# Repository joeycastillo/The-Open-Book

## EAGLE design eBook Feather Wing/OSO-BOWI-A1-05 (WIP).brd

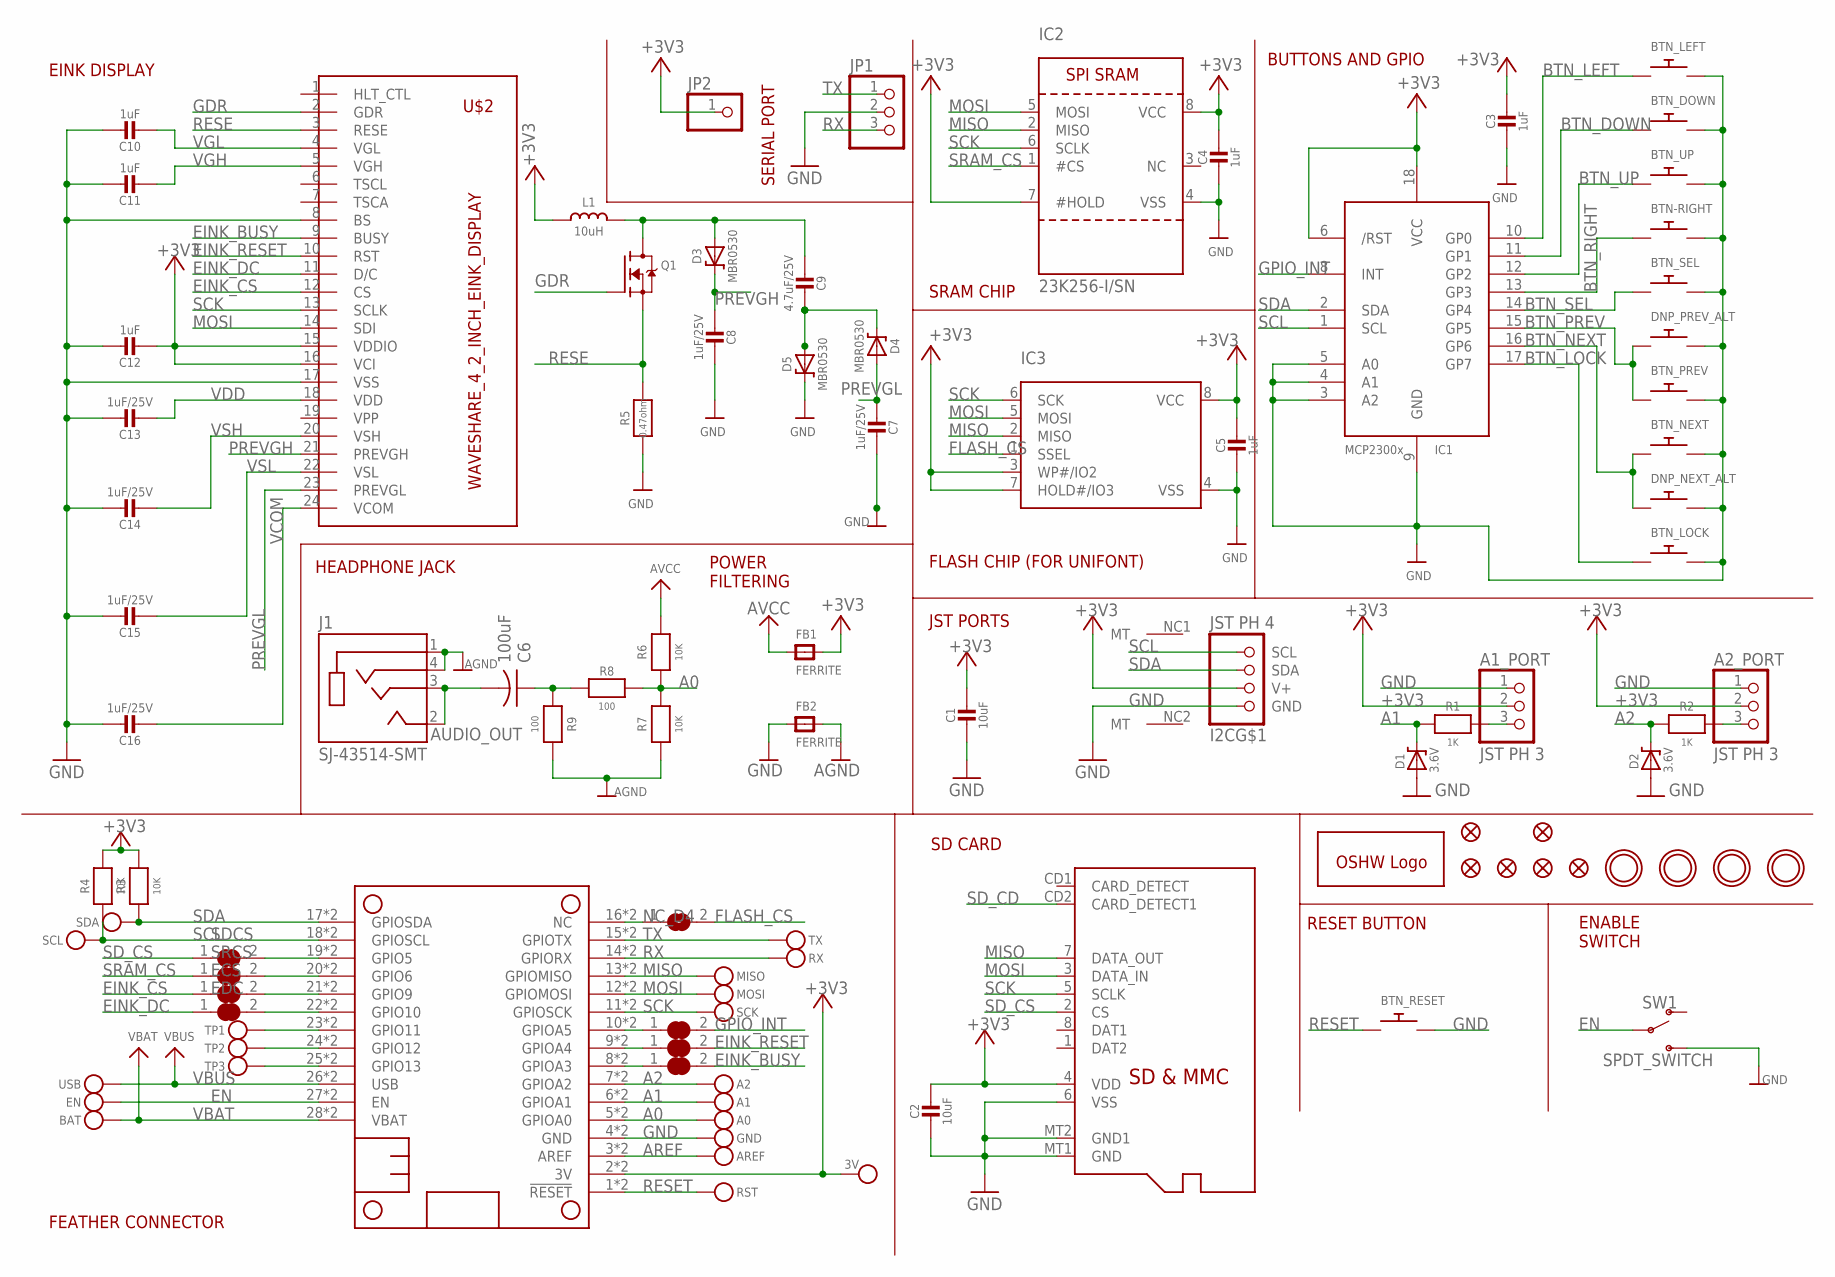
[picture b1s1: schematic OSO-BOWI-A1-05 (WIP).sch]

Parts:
3V: MICROBUILDER_TESTPOINT1.5X2.0MM_NOCREAM; MICROBUILDER_PAD-1.5X2.0
A0, A1, A2: MICROBUILDER_TESTPOINT1.5X2.0MM_NOCREAM; MICROBUILDER_PAD-1.5X2.0
A1_PORT, A2_PORT: JST PH 3; JSTPH3
AREF: MICROBUILDER_TESTPOINT1.5X2.0MM_NOCREAM; MICROBUILDER_PAD-1.5X2.0
BAT: MICROBUILDER_TESTPOINT1.5X2.0MM_NOCREAM; MICROBUILDER_PAD-1.5X2.0
BCS: SOLDERJUMPER_OPEN
BTN-RIGHT: SWITCH_PUSHBUTTONEVQ-PE; TACT_PANA-EVQ
BTN_DOWN: SWITCH_PUSHBUTTONEVQ-PE; TACT_PANA-EVQ
BTN_LEFT: SWITCH_PUSHBUTTONEVQ-PE; TACT_PANA-EVQ
BTN_LOCK: SWITCH_PUSHBUTTONC&K_KSS; BTN_CK_KSS
BTN_NEXT: SWITCH_PUSHBUTTONEVQ-PE; TACT_PANA-EVQ
BTN_PREV: SWITCH_PUSHBUTTONEVQ-PE; TACT_PANA-EVQ
BTN_RESET: SWITCH_PUSHBUTTONC&K_KSS; BTN_CK_KSS
BTN_SEL: SWITCH_PUSHBUTTONEVQ-PE; TACT_PANA-EVQ
BTN_UP: SWITCH_PUSHBUTTONEVQ-PE; TACT_PANA-EVQ
C1: 10uF; 0805-NO
C2: 10uF; 0805_10MGAP
C3, C4, C5: 1uF; 0805_10MGAP
C6: 100uF; C1210
C7, C8, C13, C14, C15, C16: 1uF/25V; 0805-NO
C9: 4.7uF/25V; 0805-NO
C10, C11, C12: 1uF; 0805-NO
D1, D2: 3.6V; SOD-123
D3, D4, D5: MBR0530; SOD-123
DNP_NEXT_ALT: SPST_TACTILE_SWITCHRA; TL3330AF130QG
DNP_PREV_ALT: SPST_TACTILE_SWITCHRA; TL3330AF130QG
EBSY: MICROBUILDER_SOLDERJUMPER_CLOSED; MICROBUILDER_SOLDERJUMPER_CLOSEDWIRE
ECS: MICROBUILDER_SOLDERJUMPER_CLOSED; MICROBUILDER_SOLDERJUMPER_CLOSEDWIRE
EDC: MICROBUILDER_SOLDERJUMPER_CLOSED; MICROBUILDER_SOLDERJUMPER_CLOSEDWIRE
EN: MICROBUILDER_TESTPOINT1.5X2.0MM_NOCREAM; MICROBUILDER_PAD-1.5X2.0
ERST: MICROBUILDER_SOLDERJUMPER_CLOSED; MICROBUILDER_SOLDERJUMPER_CLOSEDWIRE
FB1, FB2: FERRITE; 0805
FID1, FID2, FID3, FID4, FID5, FID6: FIDUCIAL_1MM
GND: MICROBUILDER_TESTPOINT1.5X2.0MM_NOCREAM; MICROBUILDER_PAD-1.5X2.0
GOLD_ORB_SM1: OSHWLOGOLOGO5MM; OSHW_5MM
I2C: JST PH 4; JSTPH4
IC1: MCP23008/SO; SO18W
IC2: 23K256-I/SN; SOIC8_150MIL
IC3: MICROBUILDER_SPIFLASH_SOIC8; MICROBUILDER_SOIC8_150MIL
INT: MICROBUILDER_SOLDERJUMPER_CLOSED; MICROBUILDER_SOLDERJUMPER_CLOSEDWIRE
J1: SJ-43514-SMT; CUI_SJ-43514-SMT
JP1: PINHD-1X3; 1X03
JP2: PINHD-1X1; 1X01
L1: 10uH; MICROBUILDER_INDUCTOR_4X4MM_NR401_BIGPADS
MICROSD: MICROSD
MISO: MICROBUILDER_TESTPOINT1.5X2.0MM_NOCREAM; MICROBUILDER_PAD-1.5X2.0
MOSI: MICROBUILDER_TESTPOINT1.5X2.0MM_NOCREAM; MICROBUILDER_PAD-1.5X2.0
MS1: MICROBUILDER_FEATHERWING_SMTDUAL; MICROBUILDER_FEATHERWING_SMT2
Q1: IRLML0100; SOT23-3
R1, R2: 1K; _0805MP
R3, R4, R6, R7: 10K; _0805MP
R5: 0.47ohm; 0805_10MGAP
R8, R9: 100; _0805MP
RST: MICROBUILDER_TESTPOINT1.5X2.0MM_NOCREAM; MICROBUILDER_PAD-1.5X2.0
RX: MICROBUILDER_TESTPOINT1.5X2.0MM_NOCREAM; MICROBUILDER_PAD-1.5X2.0
SCK: MICROBUILDER_TESTPOINT1.5X2.0MM_NOCREAM; MICROBUILDER_PAD-1.5X2.0
SCL: MICROBUILDER_TESTPOINT1.5X2.0MM_NOCREAM; MICROBUILDER_PAD-1.5X2.0
SDA: MICROBUILDER_TESTPOINT1.5X2.0MM_NOCREAM; MICROBUILDER_PAD-1.5X2.0
SDCS: MICROBUILDER_SOLDERJUMPER_CLOSED; MICROBUILDER_SOLDERJUMPER_CLOSEDWIRE
SRCS: MICROBUILDER_SOLDERJUMPER_CLOSED; MICROBUILDER_SOLDERJUMPER_CLOSEDWIRE
SW1: SPDT_SWITCH; A10767
TP1, TP2, TP3: MICROBUILDER_TESTPOINT1.5X2.0MM_NOCREAM; MICROBUILDER_PAD-1.5X2.0
TX: MICROBUILDER_TESTPOINT1.5X2.0MM_NOCREAM; MICROBUILDER_PAD-1.5X2.0
U$1, U$4, U$5, U$7: MOUNTINGHOLE2.5; MOUNTINGHOLE_2.5_PLATED
U$2: WAVESHARE_4_2_INCH_EINK_DISPLAY; EINK_DISPLAY_4_2IN
USB: MICROBUILDER_TESTPOINT1.5X2.0MM_NOCREAM; MICROBUILDER_PAD-1.5X2.0

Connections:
+3V3: 3V.P$1, A1_PORT.2, A2_PORT.2, C1.1, C2.1, C3.1, C4.1, C5.1, C12.2, FB1.2, I2C.2 (V+), IC1.6 (/RST), IC1.18 (VCC), IC2.7 (#HOLD), IC2.8 (VCC), IC3.3 (WP#/IO2), IC3.7 (HOLD#/IO3), IC3.8 (VCC), JP2.1, L1.P$1 (1), MICROSD.4 (VDD), MS1.2 (3V), MS1.2' (3V), R3.1, R4.1, U$2.15 (VDDIO), U$2.16 (VCI)
A0: A0.P$1, MS1.5 (GPIOA0), MS1.5' (GPIOA0), R6.2, R7.1, R8.1
A1: A1.P$1, D1.C, MS1.6 (GPIOA1), MS1.6' (GPIOA1), R1.2
A1_: A1_PORT.3, R1.1
A2: A2.P$1, D2.C, MS1.7 (GPIOA2), MS1.7' (GPIOA2), R2.2
A2_: A2_PORT.3, R2.1
AGND: FB2.2, J1.1 (SLEEVE), J1.4 (RING2), R7.2, R9.1
AREF: AREF.P$1, MS1.3 (AREF), MS1.3' (AREF)
AUDIO_OUT: C6.2, J1.2 (TIP), J1.3 (RING1)
AVCC: FB1.1, R6.1
BTN_DOWN: BTN_DOWN.P$1, IC1.11 (GP1)
BTN_LEFT: BTN_LEFT.P$1, IC1.10 (GP0)
BTN_LOCK: BTN_LOCK.P$1, IC1.17 (GP7)
BTN_NEXT: BTN_NEXT.P$1, DNP_NEXT_ALT.P$1, IC1.16 (GP6)
BTN_PREV: BTN_PREV.P$1, DNP_PREV_ALT.P$1, IC1.15 (GP5)
BTN_RIGHT: BTN-RIGHT.P$1, IC1.13 (GP3)
BTN_SEL: BTN_SEL.P$1, IC1.14 (GP4)
BTN_UP: BTN_UP.P$1, IC1.12 (GP2)
EINK_BUSY: EBSY.2, U$2.9 (BUSY)
EINK_CS: ECS.1, U$2.12 (CS)
EINK_DC: EDC.1, U$2.11 (D/C)
EINK_RESET: ERST.2, U$2.10 (RST)
EN: EN.P$1, MS1.27 (EN), MS1.27' (EN), SW1.P$2
FLASH_CS: BCS.2, IC3.1 (SSEL)
GDR: Q1.1 (G), U$2.2 (GDR)
GND: A1_PORT.1, A2_PORT.1, BTN-RIGHT.P$2, BTN_DOWN.P$2, BTN_LEFT.P$2, BTN_LOCK.P$2, BTN_NEXT.P$2, BTN_PREV.P$2, BTN_RESET.P$2, BTN_SEL.P$2, BTN_UP.P$2, C1.2, C2.2, C3.2, C4.2, C5.2, C7.2, C8.2, C10.1, C11.1, C12.1, C13.1, C14.1, C15.1, C16.1, D1.A, D2.A, D5.C, DNP_NEXT_ALT.P$2, DNP_PREV_ALT.P$2, FB2.1, GND.P$1, I2C.1 (GND), IC1.3 (A2), IC1.4 (A1), IC1.5 (A0), IC1.9 (GND), IC2.4 (VSS), IC3.4 (VSS), JP1.2, MICROSD.6 (VSS), MICROSD.MT1 (GND), MICROSD.MT2 (GND1), MS1.4 (GND), MS1.4' (GND), R5.2, SW1.P$3 (S), U$2.8 (BS), U$2.17 (VSS)
GPIO_INT: IC1.8 (INT), INT.2
MISO: IC2.2 (MISO), IC3.2 (MISO), MICROSD.7 (DATA_OUT), MISO.P$1, MS1.13 (GPIOMISO), MS1.13' (GPIOMISO)
MOSI: IC2.5 (MOSI), IC3.5 (MOSI), MICROSD.3 (DATA_IN), MOSI.P$1, MS1.12 (GPIOMOSI), MS1.12' (GPIOMOSI), U$2.14 (SDI)
unnamed: C6.1, R8.2, R9.2
unnamed: C9.2, D4.C, D5.A
unnamed: C9.1, D3.A, L1.P$2 (2), Q1.3 (D)
unnamed: MS1.25 (GPIO13), MS1.25' (GPIO13), TP3.P$1
unnamed: MS1.24 (GPIO12), MS1.24' (GPIO12), TP2.P$1
unnamed: MS1.23 (GPIO11), MS1.23' (GPIO11), TP1.P$1
NC_D4: BCS.1, MS1.16 (NC), MS1.16' (NC)
PREVGH: C8.1, D3.C, U$2.21 (PREVGH)
PREVGL: C7.1, D4.A, U$2.23 (PREVGL)
RESE: Q1.2 (S), R5.1, U$2.3 (RESE)
RESET: BTN_RESET.P$1, MS1.1 (!RESET), MS1.1' (!RESET), RST.P$1
RX: JP1.3, MS1.14 (GPIORX), MS1.14' (GPIORX), RX.P$1
SCK: IC2.6 (SCLK), IC3.6 (SCK), MICROSD.5 (SCLK), MS1.11 (GPIOSCK), MS1.11' (GPIOSCK), SCK.P$1, U$2.13 (SCLK)
SCL: I2C.4 (SCL), IC1.1 (SCL), MS1.18 (GPIOSCL), MS1.18' (GPIOSCL), R4.2, SCL.P$1
SDA: I2C.3 (SDA), IC1.2 (SDA), MS1.17 (GPIOSDA), MS1.17' (GPIOSDA), R3.2, SDA.P$1
SD_CD: MICROSD.CD2 (CARD_DETECT1)
SD_CS: MICROSD.2 (CS), SDCS.1
SRAM_CS: IC2.1 (#CS), SRCS.1
TX: JP1.1, MS1.15 (GPIOTX), MS1.15' (GPIOTX), TX.P$1
VBAT: BAT.P$1, MS1.28 (VBAT), MS1.28' (VBAT)
VBUS: MS1.26 (USB), MS1.26' (USB), USB.P$1
VCOM: C16.2, U$2.24 (VCOM)
VDD: C13.2, U$2.18 (VDD)
VGH: C11.2, U$2.5 (VGH)
VGL: C10.2, U$2.4 (VGL)
VSH: C14.2, U$2.20 (VSH)
VSL: C15.2, U$2.22 (VSL)
_EINK_BUSY: EBSY.1, MS1.8 (GPIOA3), MS1.8' (GPIOA3)
_EINK_CS: ECS.2, MS1.21 (GPIO9), MS1.21' (GPIO9)
_EINK_DC: EDC.2, MS1.22 (GPIO10), MS1.22' (GPIO10)
_EINK_RESET: ERST.1, MS1.9 (GPIOA4), MS1.9' (GPIOA4)
_GPIO_INT: INT.1, MS1.10 (GPIOA5), MS1.10' (GPIOA5)
_SD_CS: MS1.19 (GPIO5), MS1.19' (GPIO5), SDCS.2
_SRAM_CS: MS1.20 (GPIO6), MS1.20' (GPIO6), SRCS.2

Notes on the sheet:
FEATHER CONNECTOR
SD CARD
EINK DISPLAY
HEADPHONE JACK
RESET BUTTON
ENABLE SWITCH
POWER FILTERING
BUTTONS AND GPIO
JST PORTS
SRAM CHIP
FLASH CHIP (FOR UNIFONT)
SERIAL PORT

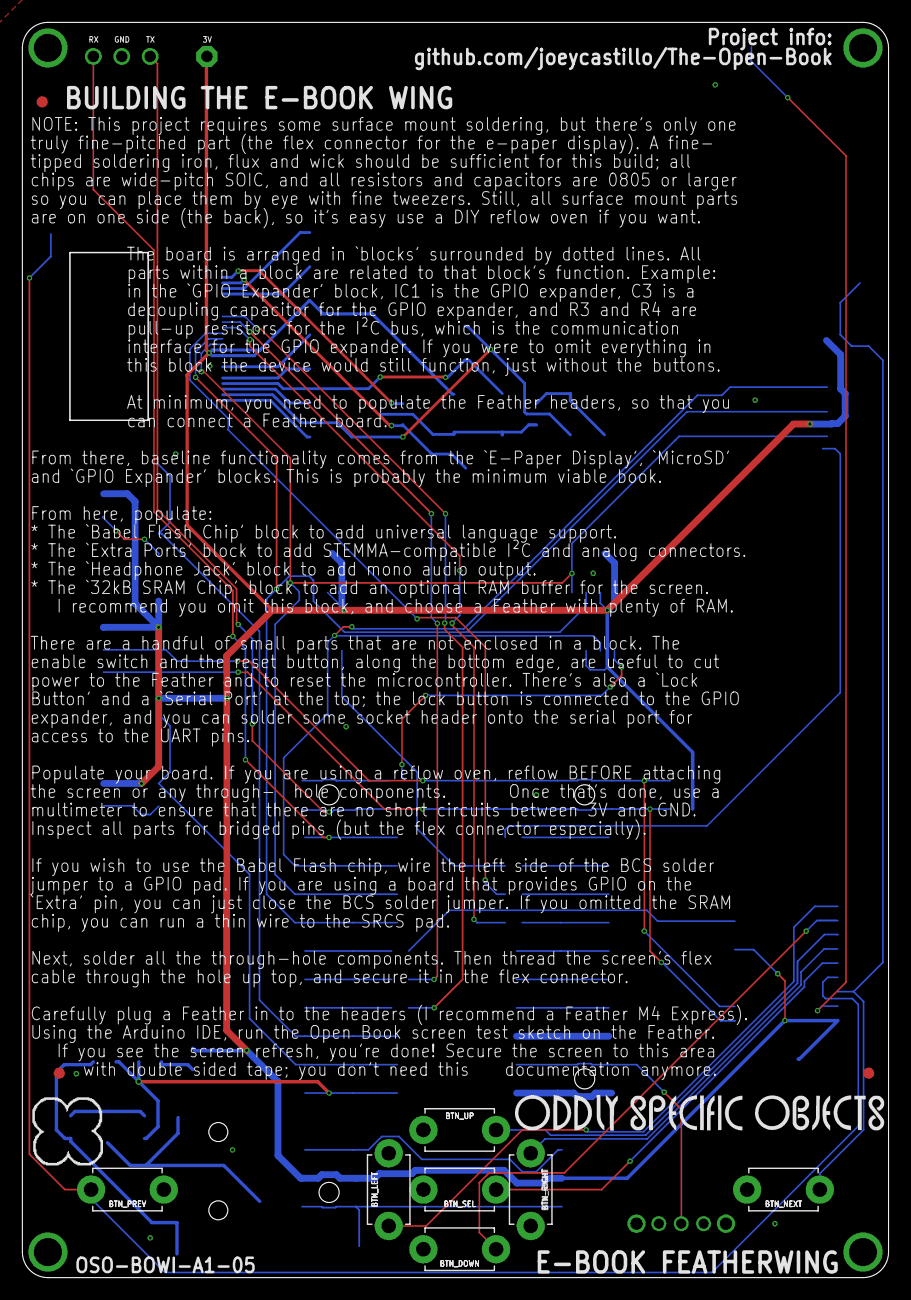
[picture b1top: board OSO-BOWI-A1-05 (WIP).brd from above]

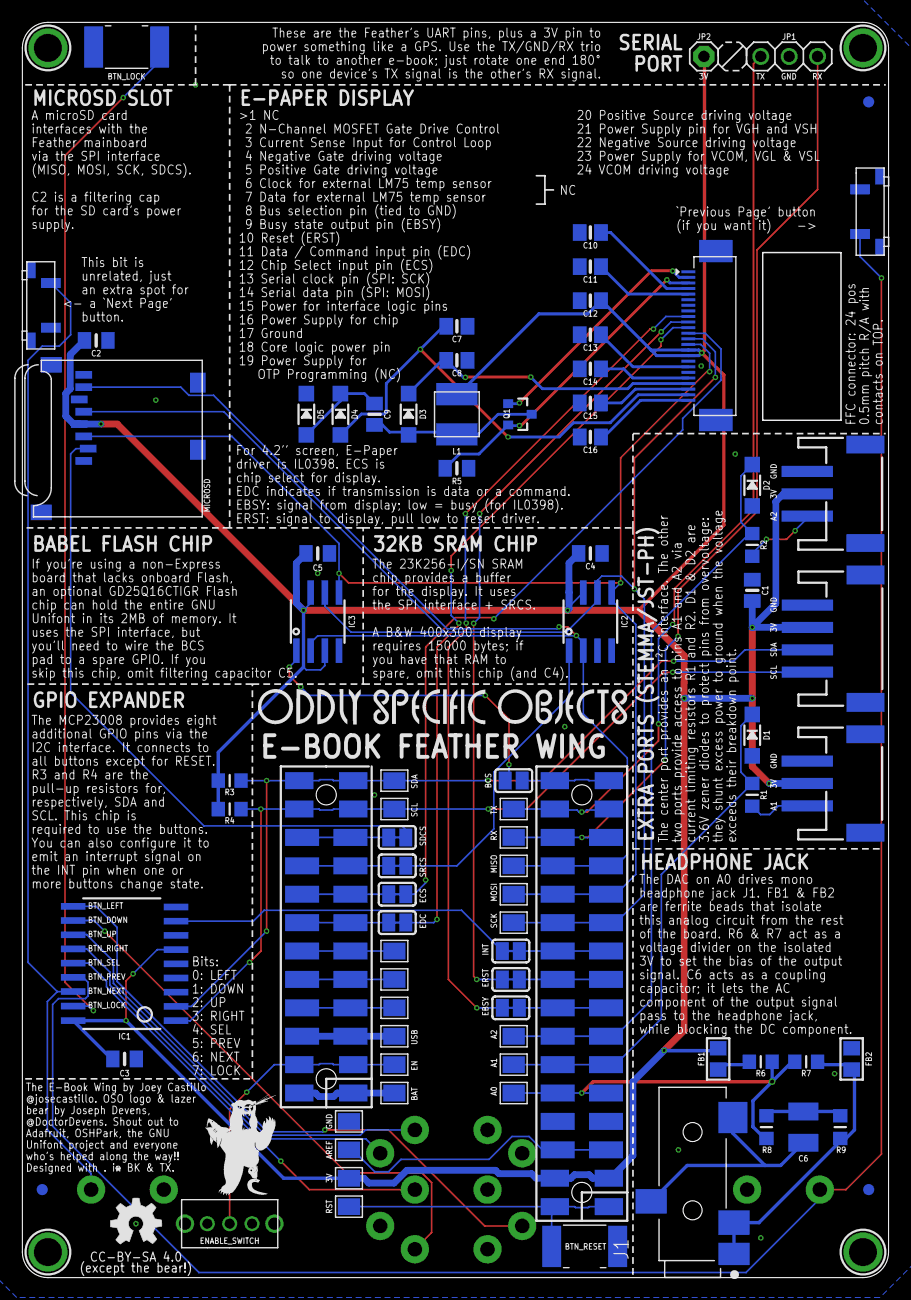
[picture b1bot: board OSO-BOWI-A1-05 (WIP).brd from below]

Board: 2 copper layers, 77.5 x 112.3 mm, 101 parts (88 on the bottom side), 62 nets.

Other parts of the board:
U$11, U$13: OSO_WORDMARK_125X1300MIL_1000DPI
U$15: OSO_BEAR_250X360MIL_1000DPI
U$44: OSO_GRAPHIC

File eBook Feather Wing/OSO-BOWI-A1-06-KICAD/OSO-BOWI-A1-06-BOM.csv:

Reference, Quantity, Value, Footprint, Datasheet
A1_PORT1 A2_PORT1 ,2,"JST PH 3","OSO-BOWI-A1-06:JSTPH3",""
BCS1 ,1,"SOLDERJUMPER_OPEN","OSO-BOWI-A1-06:SOLDERJUMPER_OPEN",""
BTN-RIGHT1 BTN_DOWN1 BTN_LEFT1 BTN_NEXT1 BTN_PREV1 BTN_SEL1 BTN_UP1 ,7,"SWITCH_PUSHBUTTONEVQ-PE","OSO-BOWI-A1-06:TACT_PANA-EVQ",""
BTN_LOCK1 BTN_RESET1 ,2,"SWITCH_PUSHBUTTONC&K_KSS","OSO-BOWI-A1-06:BTN_CK_KSS",""
C1 ,1,"10uF","OSO-BOWI-A1-06:0805-NO",""
C10 C11 C12 ,3,"1uF","OSO-BOWI-A1-06:0805-NO",""
C13 C14 C15 C16 C7 C8 ,6,"1uF/25V","OSO-BOWI-A1-06:0805-NO",""
C2 ,1,"10uF","OSO-BOWI-A1-06:0805_10MGAP",""
C3 C4 C5 ,3,"1uF","OSO-BOWI-A1-06:0805_10MGAP",""
C6 ,1,"100uF","OSO-BOWI-A1-06:C1210",""
C9 ,1,"4.7uF/25V","OSO-BOWI-A1-06:0805-NO",""
D1 D2 ,2,"3.6V","OSO-BOWI-A1-06:SOD-123",""
D3 D4 D5 ,3,"MBR0530","OSO-BOWI-A1-06:SOD-123",""
DNP_NEXT_ALT1 DNP_PREV_ALT1 ,2,"SPST_TACTILE_SWITCHRA","OSO-BOWI-A1-06:TL3330AF130QG",""
FB1 FB2 ,2,"FERRITE","OSO-BOWI-A1-06:0805",""
FID1 FID2 FID3 FID4 FID5 FID6 ,6,"FIDUCIAL_1MM","OSO-BOWI-A1-06:FIDUCIAL_1MM",""
GOLD_ORB_SM1 ,1,"OSHWLOGOLOGO5MM","OSO-BOWI-A1-06:OSHW_5MM",""
I2C1 ,1,"JST PH 4","OSO-BOWI-A1-06:JSTPH4",""
IC1 ,1,"MCP23008_SO","OSO-BOWI-A1-06:SO18W",""
IC2 ,1,"23K256-I/SN","OSO-BOWI-A1-06:SOIC8_150MIL",""
IC3 ,1,"MICROBUILDER_SPIFLASH_SOIC8","OSO-BOWI-A1-06:MICROBUILDER_SOIC8_150MIL",""
J1 ,1,"SJ-43514-SMT","OSO-BOWI-A1-06:CUI_SJ-43514-SMT",""
JP1 ,1,"PINHD-1X3","OSO-BOWI-A1-06:1X03",""
JP2 ,1,"PINHD-1X1","OSO-BOWI-A1-06:1X01",""
L1 ,1,"10uH","OSO-BOWI-A1-06:MICROBUILDER_INDUCTOR_4X4MM_NR401_BIGPADS",""
MICROSD1 ,1,"MICROSD","OSO-BOWI-A1-06:MICROSD",""
MS1 ,1,"MICROBUILDER_FEATHERWING_SMTDUAL_NOLINES","OSO-BOWI-A1-06:MICROBUILDER_FEATHERWING_SMT2_NOLINES",""
Q1 ,1,"IRLML0100","OSO-BOWI-A1-06:SOT23-3",""
R1 R2 ,2,"1K","OSO-BOWI-A1-06:_0805MP",""
R5 ,1,"0.47ohm","OSO-BOWI-A1-06:0805_10MGAP",""
R10 R11 R12 R13 R3 R4 R6 R7 ,8,"10K","OSO-BOWI-A1-06:_0805MP",""
R8 R9 ,2,"100","OSO-BOWI-A1-06:_0805MP",""
EBSY1 ECS1 EDC1 ERST1 INT1 SDCS1 SRCS1 ,7,"MICROBUILDER_SOLDERJUMPER_CLOSED","OSO-BOWI-A1-06:MICROBUILDER_SOLDERJUMPER_CLOSEDWIRE",""
SW1 ,1,"SPDT_SWITCH","OSO-BOWI-A1-06:A10767",""
3V3 A0 A1 A2 AREF1 BAT1 EN1 GND1 MISO1 MOSI1 RST1 RX1 SCK1 SCL1 SDA1 TP1 TP2 TP3 TX1 USB1 ,20,"MICROBUILDER_TESTPOINT1.5X2.0MM_NOCREAM","OSO-BOWI-A1-06:MICROBUILDER_PAD-1.5X2.0",""
U$1 U$4 U$5 U$7 ,4,"MOUNTINGHOLE2.5","OSO-BOWI-A1-06:MOUNTINGHOLE_2.5_PLATED",""
U$2 ,1,"WAVESHARE_4_2_INCH_EINK_DISPLAY","OSO-BOWI-A1-06:EINK_DISPLAY_4_2IN",""

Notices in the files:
eBook Feather Wing/OSO-BOWI-A1-05 (WIP).brd:
CC-BY-SA 4.0
